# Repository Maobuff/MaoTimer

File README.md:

# MaoTimer
A small kitchen timer for driving 12V loads. Based on MiniF4 with 1.3" OLED screen

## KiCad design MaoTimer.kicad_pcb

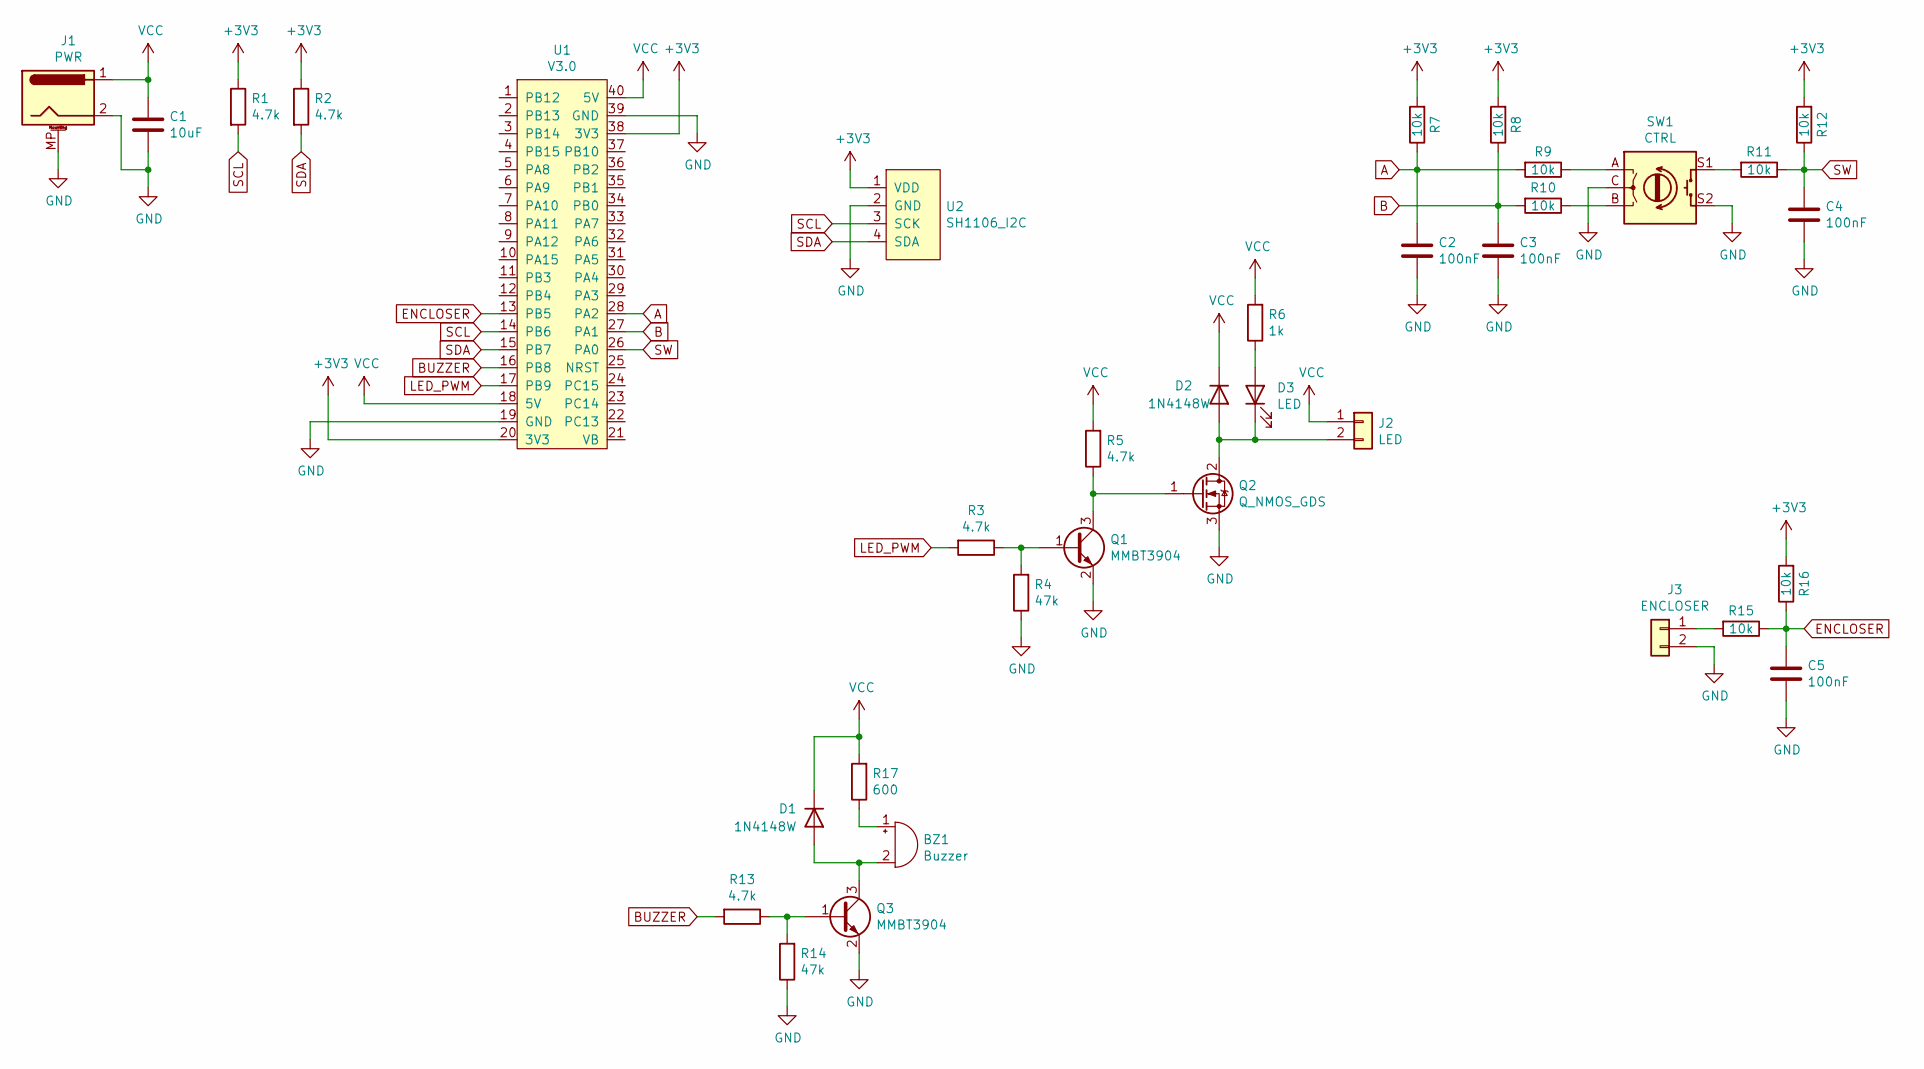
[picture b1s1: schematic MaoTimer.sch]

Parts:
BZ1: Buzzer; Buzzer_12x9.5RM7.6
C1: 10uF; C_1206_3216Metric_Pad1.33x1.80mm_HandSolder
C2, C3, C4, C5: 100nF; C_1206_3216Metric_Pad1.33x1.80mm_HandSolder
D1, D2: 1N4148W; D_SOD-123
D3: LED; LED_D5.0mm
J1: PWR; BarrelJack_CUI_PJ-102AH_Horizontal
J2: LED; PinSocket_1x02_P2.54mm_Vertical
J3: ENCLOSER; PinSocket_1x02_P2.54mm_Vertical
Q1, Q3: MMBT3904; SOT-23
Q2: Q_NMOS_GDS; TO-220-3_Horizontal_TabDown
R1, R2, R3, R5, R13: 4.7k; R_1206_3216Metric_Pad1.30x1.75mm_HandSolder
R4, R14: 47k; R_1206_3216Metric_Pad1.30x1.75mm_HandSolder
R6: 1k; R_1206_3216Metric_Pad1.30x1.75mm_HandSolder
R7, R8, R9, R10, R11, R12, R15, R16: 10k; R_1206_3216Metric_Pad1.30x1.75mm_HandSolder
R17: 600; R_1206_3216Metric_Pad1.30x1.75mm_HandSolder
SW1: CTRL; RotaryEncoder_Alps_EC11E-Switch_Vertical_H20mm
U1: V3.0; MiniF4_V3.0
U2: SH1106_I2C

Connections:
+3V3: R1.1, R2.1, R7.2, R8.2, R12.2, R16.2, U1.20 (3V3), U1.38 (3V3), U2.1 (VDD)
A: C2.1, R7.1, R9.2, U1.28 (PA2)
B: C3.1, R8.1, R10.2, U1.27 (PA1)
BUZZER: R13.2, U1.16 (PB8)
ENCLOSER: C5.1, R15.1, R16.1, U1.13 (PB5)
GND: C1.2, C2.2, C3.2, C4.2, C5.2, J1.2, J1.MP (MountPin), J3.2, Q1.2 (E), Q2.3 (S), Q3.2 (E), R4.1, R14.1, SW1.C, SW1.S2, U1.19 (GND), U1.39 (GND), U2.2 (GND)
LED_PWM: R3.2, U1.17 (PB9)
unnamed: BZ1.1 (-), R17.1
unnamed: BZ1.2 (+), D1.2 (A), Q3.3 (C)
unnamed: D2.2 (A), D3.1 (K), J2.2, Q2.2 (D)
unnamed: D3.2 (A), R6.1
unnamed: J3.1, R15.2
unnamed: Q1.1 (B), R3.1, R4.2
unnamed: Q1.3 (C), Q2.1 (G), R5.1
unnamed: Q3.1 (B), R13.1, R14.2
unnamed: R9.1, SW1.A
unnamed: R10.1, SW1.B
unnamed: R11.2, SW1.S1
SCL: R1.2, U1.14 (PB6), U2.3 (SCK)
SDA: R2.2, U1.15 (PB7), U2.4 (SDA)
SW: C4.1, R11.1, R12.1, U1.26 (PA0)
VCC: C1.1, D1.1 (K), D2.1 (K), J1.1, J2.1, R5.2, R6.2, R17.2, U1.18 (5V), U1.40 (5V)

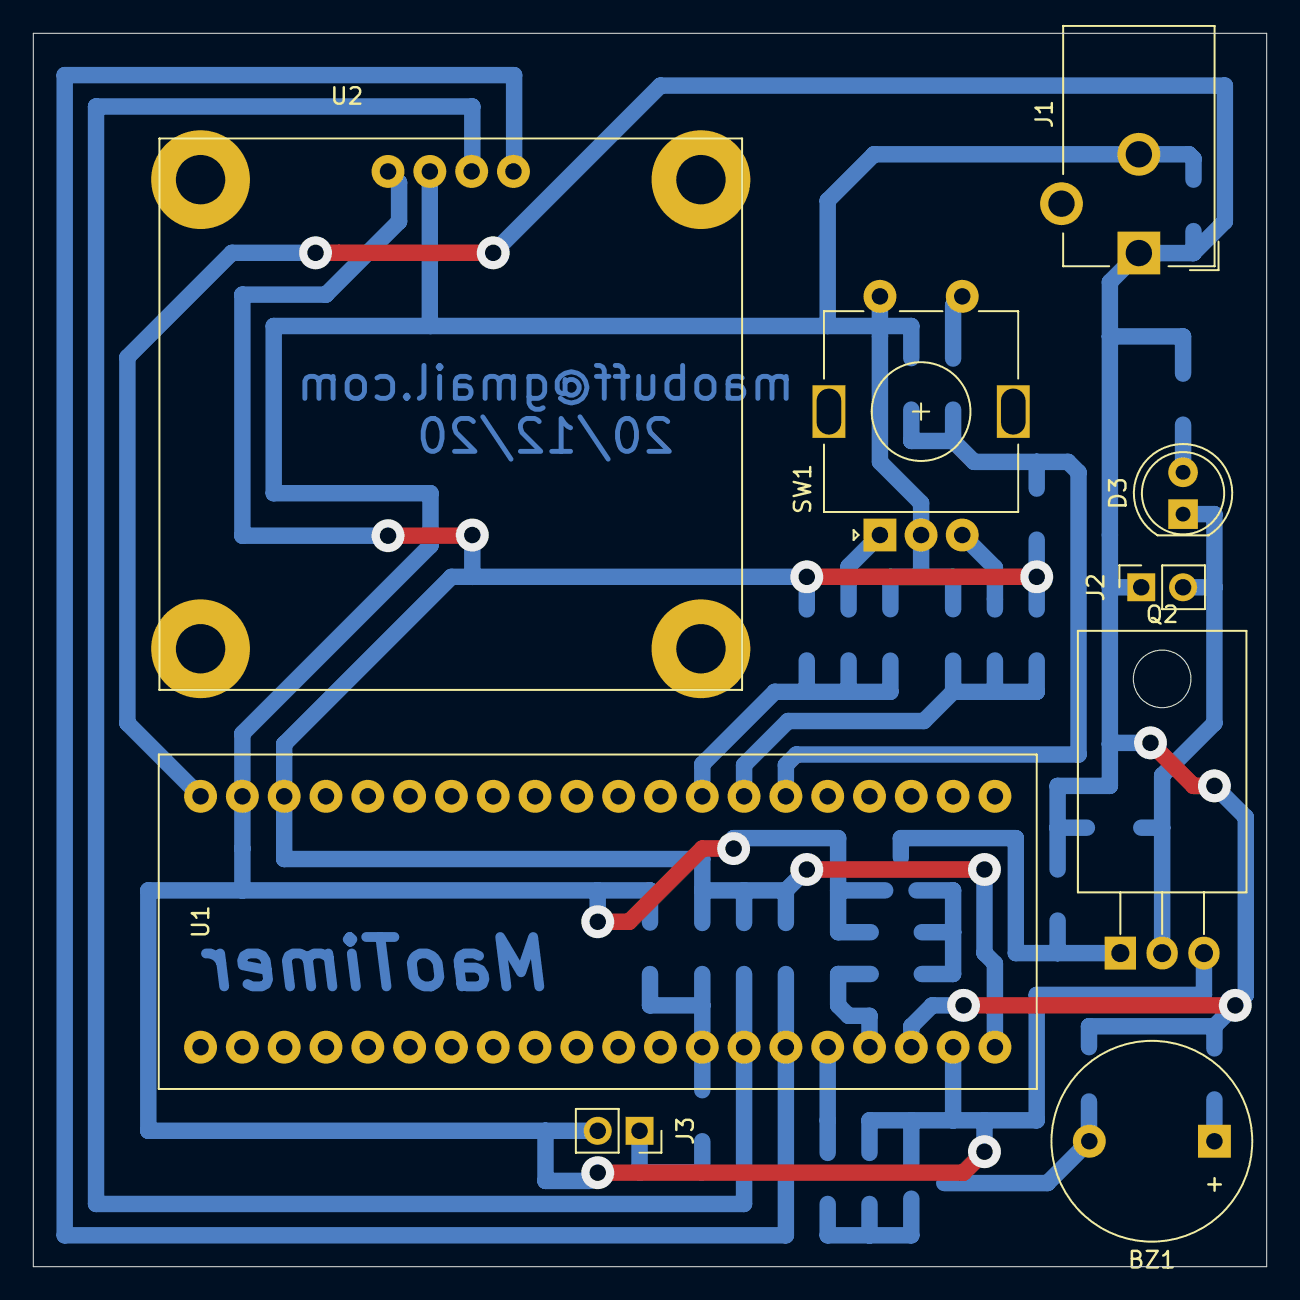
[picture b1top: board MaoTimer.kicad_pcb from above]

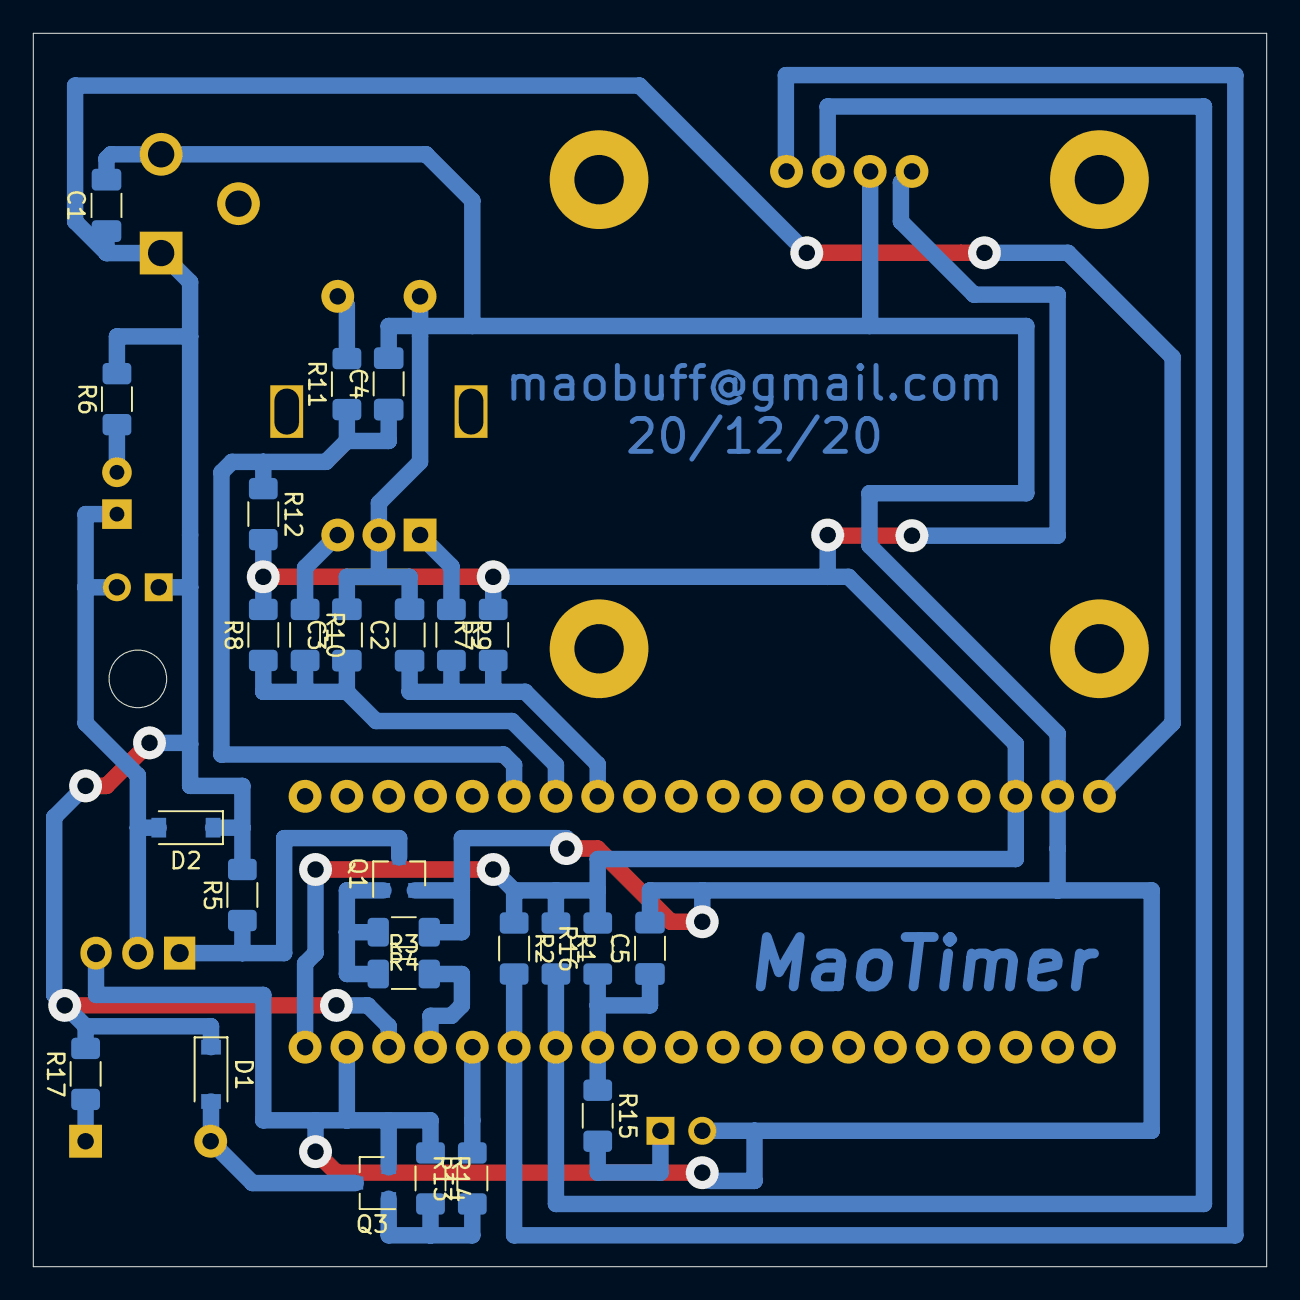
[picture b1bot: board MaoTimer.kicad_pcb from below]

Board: 2 copper layers, 74.9 x 74.9 mm, 35 parts (26 on the bottom side), 22 nets.

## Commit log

2020-12-19 feat: hardware ready for production
2020-12-19 feat: readme
2020-12-20 fix: silkscreen
